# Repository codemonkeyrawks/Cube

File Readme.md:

Led Cube Project:

#### Folder Structure:

    Main Project:
    /CAD - CAD Files for the Cube
    /Circuit - Electrical Hookup Guide
    /Code - TFT Display, Music Board, Lights Code
    /Pics - Pictures of the Build
    /Presentation - Slide Show of Build
    readme.md - Getting Started Guide
    
    Testing:
    .travis.yml - Used for Testing Only (Checks if Code Passes or Not)

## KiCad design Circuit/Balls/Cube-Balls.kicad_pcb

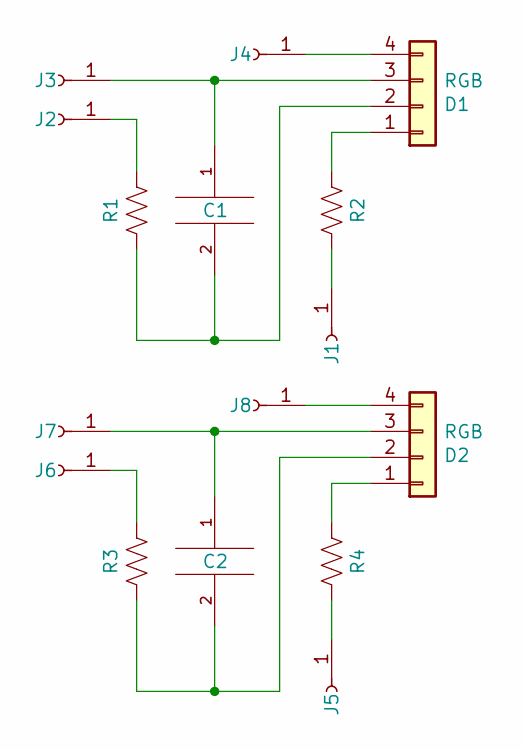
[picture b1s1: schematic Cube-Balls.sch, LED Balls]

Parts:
C1, C2: 0.1uF; R_Axial_DIN0204_L3.6mm_D1.6mm_P2.54mm_Vertical
D1, D2: RGB; SolderWirePad_1x04_P3.175mm_Drill0.8mm
J1, J5: IN; SolderWirePad_1x01_Drill1mm
J2, J6: VCC; SolderWirePad_1x01_Drill1mm
J3, J7: GND; SolderWirePad_1x01_Drill1mm
J4, J8: OUT; SolderWirePad_1x01_Drill1mm
R1, R3: 100; R_Axial_DIN0204_L3.6mm_D1.6mm_P2.54mm_Vertical
R2, R4: 10; R_Axial_DIN0204_L3.6mm_D1.6mm_P2.54mm_Vertical

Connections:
unnamed: C1.1, D1.3, J3.1
unnamed: C1.2, D1.2, R1.2
unnamed: C2.1, D2.3, J7.1
unnamed: C2.2, D2.2, R3.2
unnamed: D1.1, R2.2
unnamed: D1.4, J4.1
unnamed: D2.1, R4.2
unnamed: D2.4, J8.1
unnamed: J1.1, R2.1
unnamed: J2.1, R1.1
unnamed: J5.1, R4.1
unnamed: J6.1, R3.1

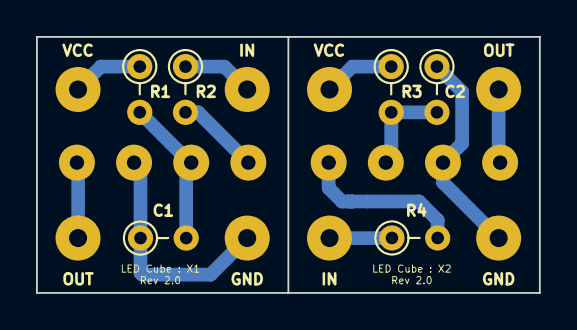
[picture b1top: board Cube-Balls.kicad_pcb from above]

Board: 2 copper layers, 27.9 x 14.2 mm, 16 parts (0 on the bottom side), 12 nets.

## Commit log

2018-11-23 Initial Code
2018-11-28 Add: TFT Display: Sample
2018-12-02 Add: Licence File
2018-12-13 Init: LED Cube Code
